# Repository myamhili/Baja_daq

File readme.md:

# Baja SAE Central Data Acquisition (DAQ) Node

A custom, ruggedized telemetry and data logging PCB engineered for the University of Waterloo Baja SAE racing vehicle. 

Unlike standard microcontroller breakout boards, this DAQ node is designed to survive the harsh electrical and mechanical environment of an automotive chassis. It features a 4-layer load-dump protected layout, dedicated hardware for high-speed logging, and a real-time FreeRTOS firmware architecture.

## ⚙️ Hardware Architecture
* **Microcontroller:** STM32F405RGTx (ARM Cortex-M4) handling real-time sensor polling and SDIO data pipelines.
* **PCB Stackup:** 4-Layer board (Signal, Solid Ground, Split Power, Signal) optimized for signal integrity, return paths, and thermal dissipation.

## 🔋 Automotive-Grade Power System
The board interfaces directly with the vehicle's 12V starter battery and is hardened against off-road electrical surges:
* **Surge Protection:** Input clamped by an SMAJ15A TVS Diode with localized solid copper pour spillways to instantly shunt 60V load dumps to the ground plane.
* **Analog Rail (5V):** L7805 linear regulator feeding suspension and rotary sensors with a clean, heavily filtered reference voltage.
* **Digital Rail (3.3V):** AMS1117 LDO isolated with dedicated bulk tantalum/ceramic decoupling arrays to prevent STM32 brownouts under severe chassis vibration.

## 📡 Sensor & Communication Interfaces
* **Vehicle Network:** CAN Bus (TJA1051T transceiver) acting as a non-blocking broadcast node for dashboard telemetry, timed via an 8MHz external crystal.
* **Inertial Tracking:** On-board 6-axis IMU (ISM330DHCX) communicating via high-speed SPI.
* **Telemetry Logging:** MicroSD card slot wired via 4-bit SDIO with 47k pull-up stability arrays for reliable 100Hz writes.
* **External I/O (Locking Molex Connectors):** * Front & Rear Suspension Travel (Generic 3-pin ADC)
    * Engine & Secondary CVT RPM (Hardware Timers / Input Capture)
    * Belt Temperature Probes (I2C)

## 💻 Firmware Design (FreeRTOS)
The system runs a custom C firmware utilizing the STM32 HAL and CMSIS-RTOS.
* **Decoupled Logging:** A high-priority sensor task handles SPI/I2C polling and mathematically derives ground speed from timer deltas. Data is formatted and pushed to a FreeRTOS queue.
* **Non-Blocking File I/O:** A lower-priority FatFs SD Writer task pulls from the queue to write to the MicroSD card, ensuring that standard file-system latency does not freeze the 100Hz real-time data gathering loop.
* **Data Protection:** Implements an automated 15-minute file rotation state machine to prevent total file corruption in the event of a sudden power loss or rollover.

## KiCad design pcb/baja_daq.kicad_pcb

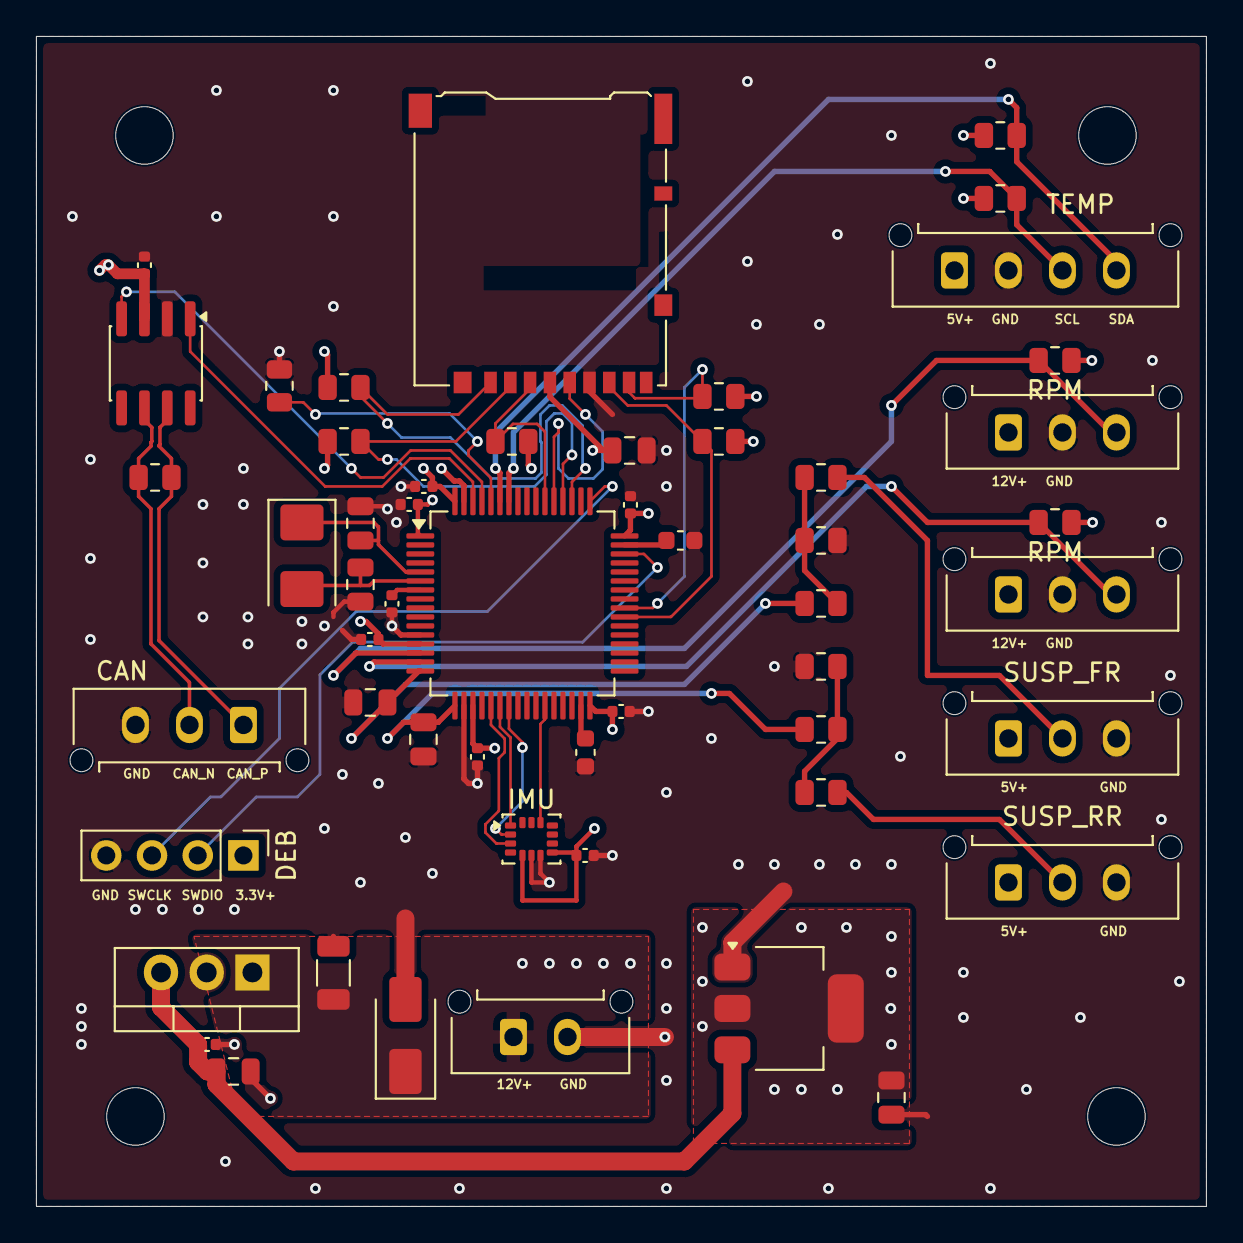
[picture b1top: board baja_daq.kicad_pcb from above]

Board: 4 copper layers, 65.0 x 65.0 mm, 57 parts (0 on the bottom side), 36 nets.

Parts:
C1, C2: 22pF; C_0805_2012Metric
C3, C4: 4.7uF; C_0805_2012Metric
C5, C6, C7, C8, C9, C10, C13, C14, C15, C19: 100nF; C_0402_1005Metric
C11, C12: 2.2uF; C_0603_1608Metric
C16, C18: 10uF; C_0805_2012Metric
C17: 10uF; C_1206_3216Metric
C20: 22uF; C_0805_2012Metric
CAN: Conn_01x03; Molex_Micro-Fit_3.0_43650-0315_1x03_P3.00mm_Vertical
D1: SMAJ15A; D_SMA
DEB: Conn_01x04; PinHeader_1x04_P2.54mm_Vertical
H1, H2, H3, H4: MountingHole; MountingHole_3.2mm_M3
IMU: ISM330DHCX; LGA-14_3x2.5mm_P0.5mm_LayoutBorder3x4y
J1: Micro_SD_Card; microSD_HC_Hirose_DM3AT-SF-PEJM5
J3, J4: Conn_01x03; Molex_Micro-Fit_3.0_43650-0315_1x03_P3.00mm_Vertical
J7: Conn_01x02; Molex_Micro-Fit_3.0_43650-0215_1x02_P3.00mm_Vertical
R1: 10k; R_0805_2012Metric
R2, R3, R4, R5, R6: 47k; R_0805_2012Metric
R7: 120Ω; R_0805_2012Metric
R8, R9: 2.2k; R_0805_2012Metric
R12, R15: 1.7k; R_0805_2012Metric
R13, R16: 3.3k; R_0805_2012Metric
R14, R17: 1k; R_0805_2012Metric
RPM: 10k; R_0805_2012Metric
RPM#2: 10k; R_0805_2012Metric
SUSP_FR: Conn_01x03; Molex_Micro-Fit_3.0_43650-0315_1x03_P3.00mm_Vertical
SUSP_RR: Conn_01x03; Molex_Micro-Fit_3.0_43650-0315_1x03_P3.00mm_Vertical
TEMP: Conn_01x04; Molex_Micro-Fit_3.0_43650-0415_1x04_P3.00mm_Vertical
U1: STM32F405RGTx; LQFP-64_10x10mm_P0.5mm
U2: TJA1051T; SOIC-8_3.9x4.9mm_P1.27mm
U4: L7805; TO-220-3_Vertical
U5: AMS1117-3.3; SOT-223-3_TabPin2
Y1: 8MHz; Crystal_SMD_5032-2Pin_5.0x3.2mm

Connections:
+3V3_DIG: C5.1, C6.1, C7.1, C8.1, C9.1, C10.1, C14.1, C16.1, C20.1, DEB.1, IMU.5, IMU.8, J1.4, R2.1, R3.1, R4.1, R5.1, R6.1, R8.1, R9.1, RPM.1, RPM#2.1, U1.1, U1.13, U1.19, U1.32, U1.48, U1.64, U5.2
+5V_ANA: C15.1, C18.1, C19.1, SUSP_FR.1, SUSP_RR.1, TEMP.1, U2.3, U4.3, U5.3
+12V_BATT: C17.1, D1.1, J3.1, J4.1, J7.1, U4.1
CAN_N: CAN.2, R7.2, U2.6
CAN_P: CAN.1, R7.1, U2.7
GND: C1.2, C2.2, C3.2, C4.2, C5.2, C6.2, C7.2, C8.2, C9.2, C10.2, C11.2, C12.2, C13.2, C14.2, C15.2, C16.2, C17.2, C18.2, C19.2, C20.2, CAN.3, D1.2, DEB.4, IMU.6, IMU.7, J1.6, J3.2, J4.2, J7.2, R1.2, R13.2, R16.2, SUSP_FR.3, SUSP_RR.3, TEMP.2, U1.12, U1.18, U1.63, U2.2, U4.2, U5.1
I2C_SCL: R8.2, TEMP.3, U1.58
I2C_SDA: R9.2, TEMP.4, U1.59
unnamed: R1.1, U1.60
unnamed: DEB.2, U1.46
unnamed: DEB.3, U1.49
unnamed: C1.1, U1.5, Y1.1
unnamed: C2.1, U1.6, Y1.2
unnamed: J1.7, R2.2, U1.39
unnamed: J1.8, R3.2, U1.40
unnamed: J1.1, R4.2, U1.51
unnamed: J1.2, R5.2, U1.52
unnamed: J1.5, U1.53
unnamed: J1.3, R6.2, U1.54
unnamed: U1.62, U2.1
unnamed: U1.61, U2.4
unnamed: C11.1, U1.31
unnamed: C12.1, U1.47
unnamed: C13.1, U1.7
RPM_ENG: J3.3, RPM.2, U1.14
RPM_SEC: J4.3, RPM#2.2, U1.15
SPI_CS: IMU.12, U1.27
SPI_MISO: IMU.1, U1.22
SPI_MOSI: IMU.2, U1.23
SPI_SCK: IMU.3, U1.21
SUSP_FR_DIV: R12.2, R13.1, R14.1
SUSP_FR_FLT: C3.1, R14.2, U1.16
SUSP_FR_RAW: R12.1, SUSP_FR.2
SUSP_RR_DIV: R15.2, R16.1, R17.1
SUSP_RR_FLT: C4.1, R17.2, U1.17
SUSP_RR_RAW: R15.1, SUSP_RR.2

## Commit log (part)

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2026-06-12 initial
2026-06-12 added images
2026-06-12 second
2026-06-12 replaced images
2026-06-12 replaced image
2026-06-19 modified layer3 (power split)
2026-06-30 uploaded full project
2026-06-30 added firmware architecture image
    Added an image of the firmware architecture to the readme.
